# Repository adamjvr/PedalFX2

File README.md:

# PedalFX2
New version of PedalFX for 1590 enclosures

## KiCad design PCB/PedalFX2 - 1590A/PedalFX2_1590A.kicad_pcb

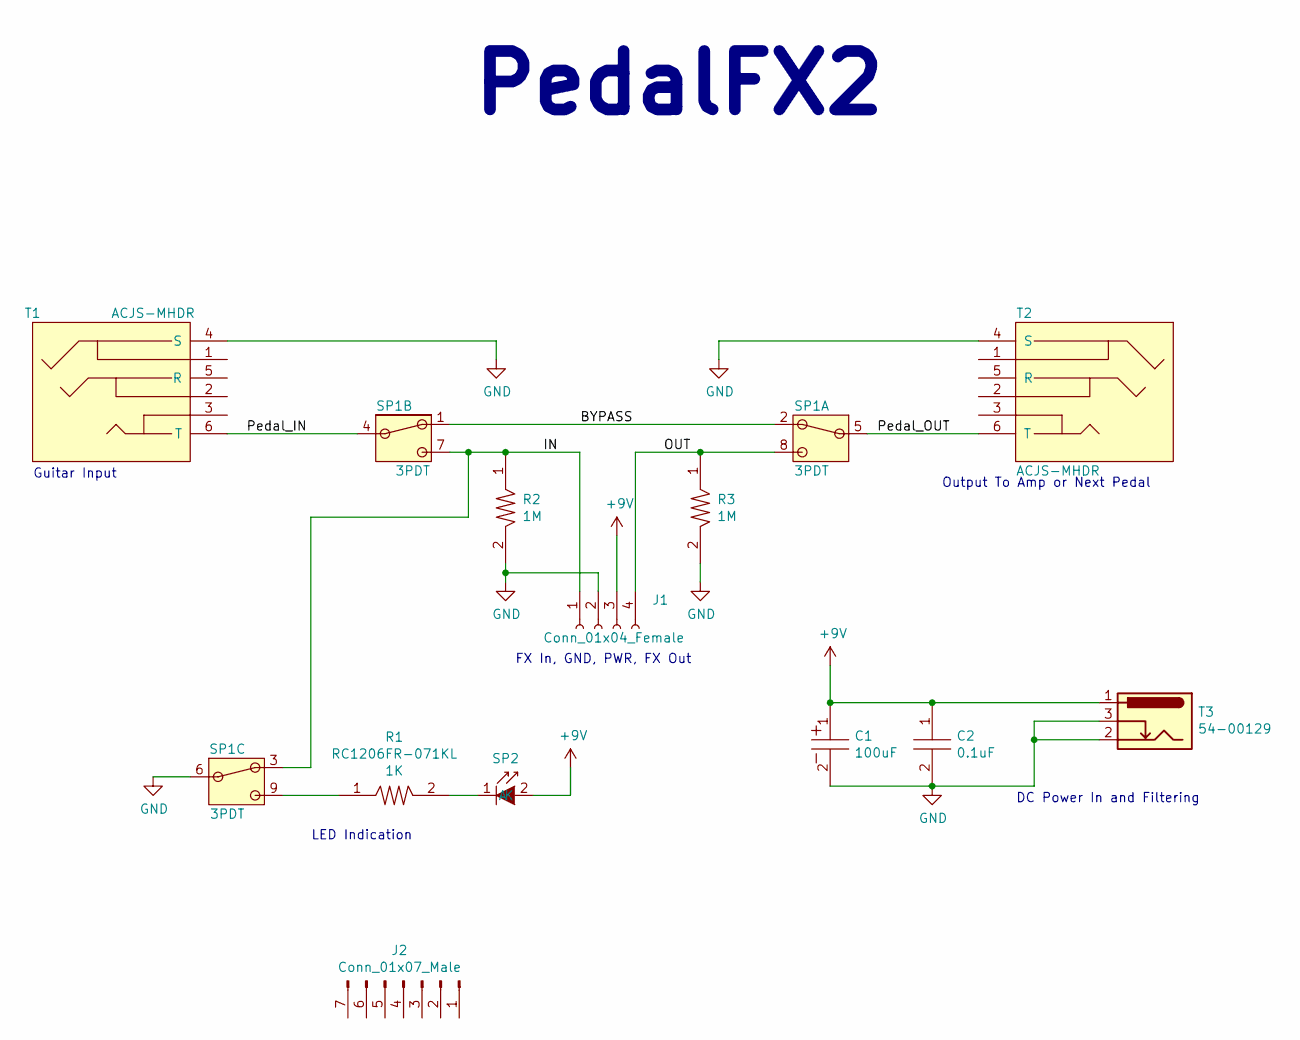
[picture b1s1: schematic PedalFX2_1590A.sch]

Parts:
C1: UFW1H101MPD; CP_Radial_D8.0mm_P3.50mm; Tolerance 20%; Voltage 50V; MFR# UFW1H101MPD
C2: CL21B104KCFNNNE; C0805; Tolerance 10%; Voltage 100V; MFR# CL21B104KCFNNNE
J1: Conn_01x04_Female; PinHeader_1x04_P2.54mm_Vertical
J2: Conn_01x07_Male; Pin_Header_Straight_1x07_Pitch2.54mm
R1: RC1206FR-071KL; R1206; Tolerance 1%; Voltage *; MFR# RC1206FR-071KL
R2, R3: RC1206FR-071ML; R1206; Tolerance 1%; Voltage *; MFR# RC1206FR-071ML
SP1: 3PDT-StompSwitch_Alt; Switches_Stomp_Switch_3PDT; Tolerance *; Voltage *; MFR# *
SP2: HLMP-4700-C0002; LED_D5.0mm; Tolerance *; Voltage 1.7V; MFR# HLMP-4700-C0002
T1, T2: ACJS-MHDR; Tolerance *; Voltage *; MFR# ACJS-MHDR
T3: 54-00129; BarrelJack_Horizontal; Tolerance *; Voltage 48V; MFR# 54-00129

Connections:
+9V: C1.1, C2.1, J1.3, SP2.2 (A), T3.1
/BYPASS: SP1.1, SP1.2
/IN: J1.1, R2.1, SP1.3, SP1.7
/OUT: J1.4, R3.1, SP1.8
/Pedal_IN: SP1.4, T1.6 (T)
/Pedal_OUT: SP1.5, T2.6 (T)
GND: C1.2, C2.2, J1.2, R2.2, R3.2, SP1.6, T1.4 (S), T2.4 (S), T3.2, T3.3
unnamed: R1.1, SP1.9
unnamed: R1.2, SP2.1 (K)

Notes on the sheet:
Guitar Input
Output To Amp or Next Pedal
FX In, GND, PWR, FX Out
LED Indication
PedalFX2
DC Power In and Filtering

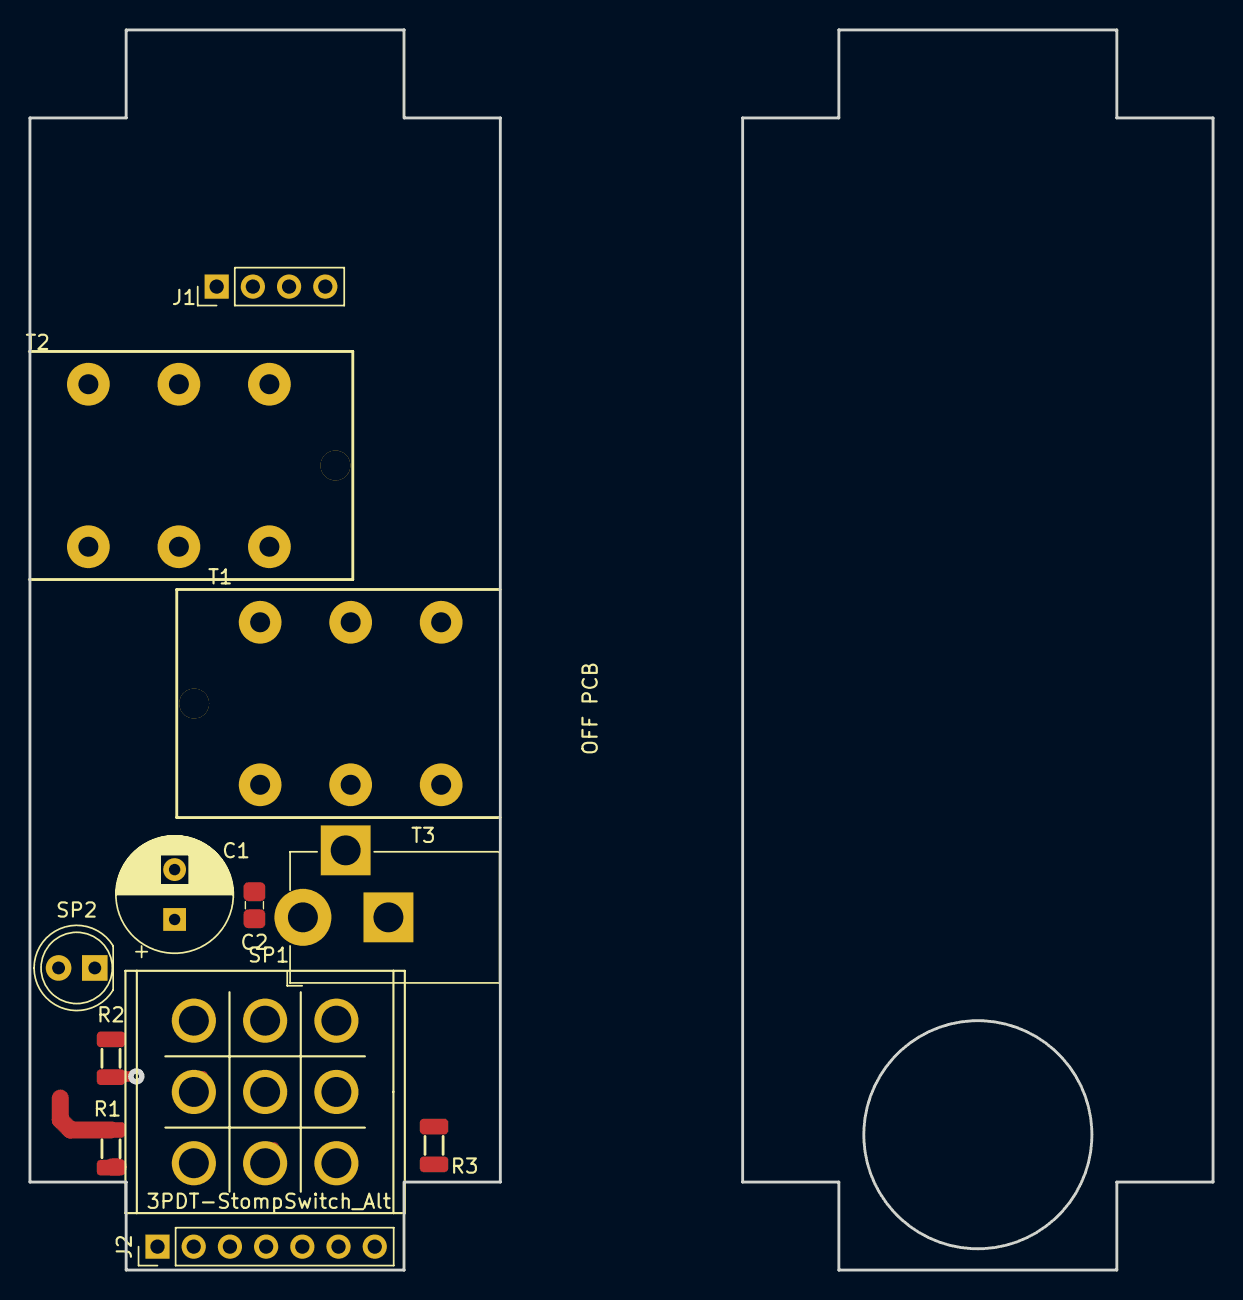
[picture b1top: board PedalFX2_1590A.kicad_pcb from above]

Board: 2 copper layers, 33.0 x 87.0 mm, 12 parts (0 on the bottom side), 9 nets.

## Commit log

2019-04-29 Done
    First pass of schematic and PCB finished
2019-04-29 Credit
    Credit original project
2019-05-04 Minor Tweaks
    Minor tweaks to PCB
2019-05-09 Added new version
    1590BB version added
2019-05-11 1590BB
    1590BB variants in progress. Horizontal one finished, working on vertical. TRS jack footprint needs adjustment.
2019-05-11 1590BB Verticalk
    Vertical variant completed, incorporated adjuistments to TRS footprint, others will be updated to follow.
2019-05-11 Goofed
    Goofed internal connector flipped and jacks not flush with housing. All fixed now, all boards redone.
2019-05-11 Templates
    Added pedal templates for each size of PedalFX2
2019-11-30 New Size
    New size added 1590N1
2020-05-03 Various versions added and editted
    Added 1590N1 size and 1590A has been editted.
2020-12-11 Mincor tweaks
    minor tweaks
